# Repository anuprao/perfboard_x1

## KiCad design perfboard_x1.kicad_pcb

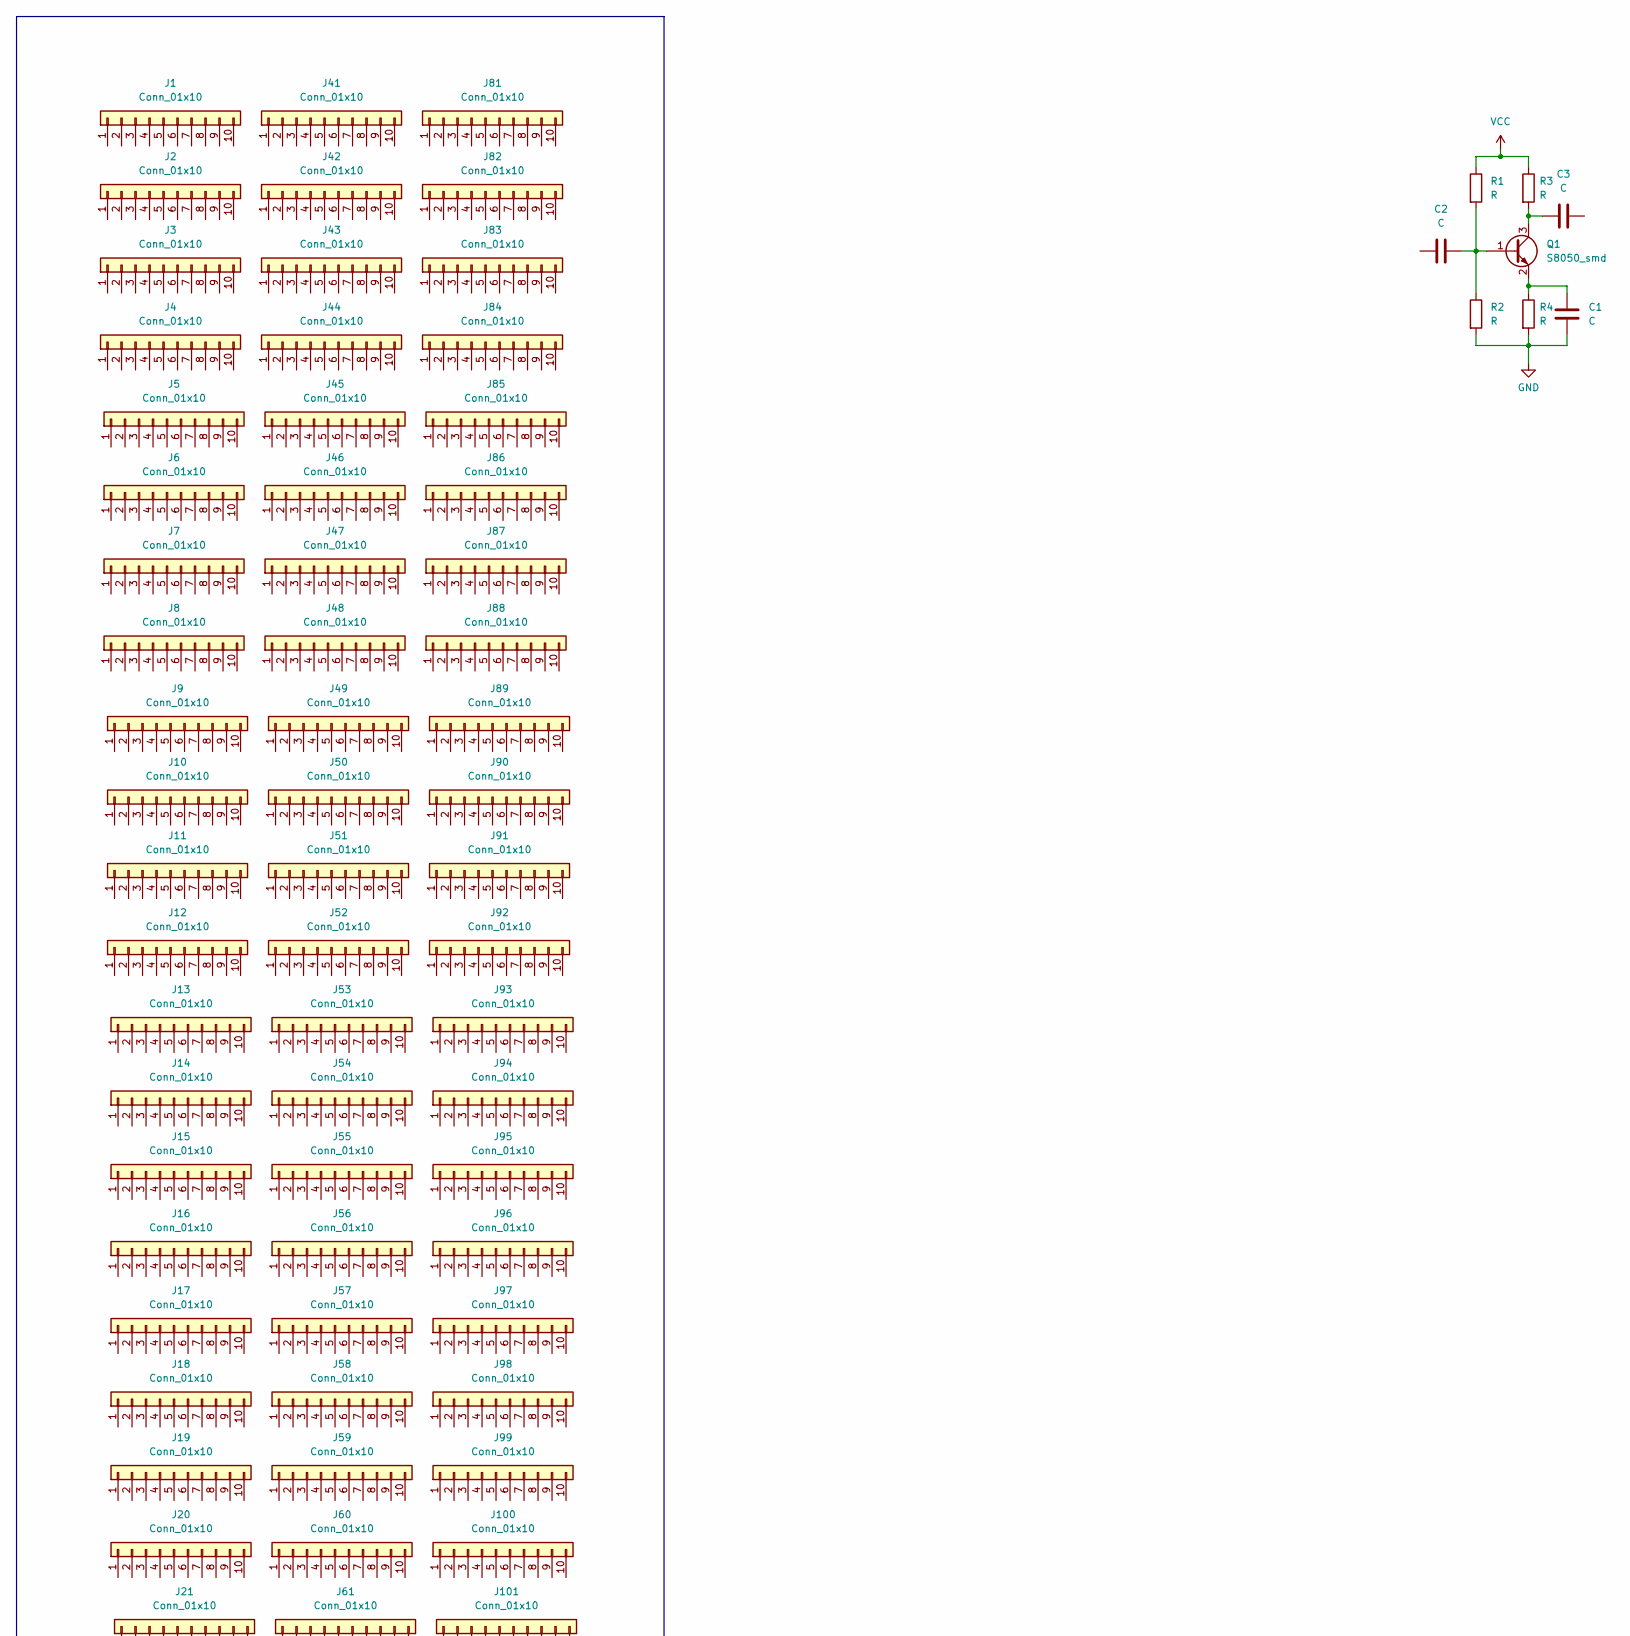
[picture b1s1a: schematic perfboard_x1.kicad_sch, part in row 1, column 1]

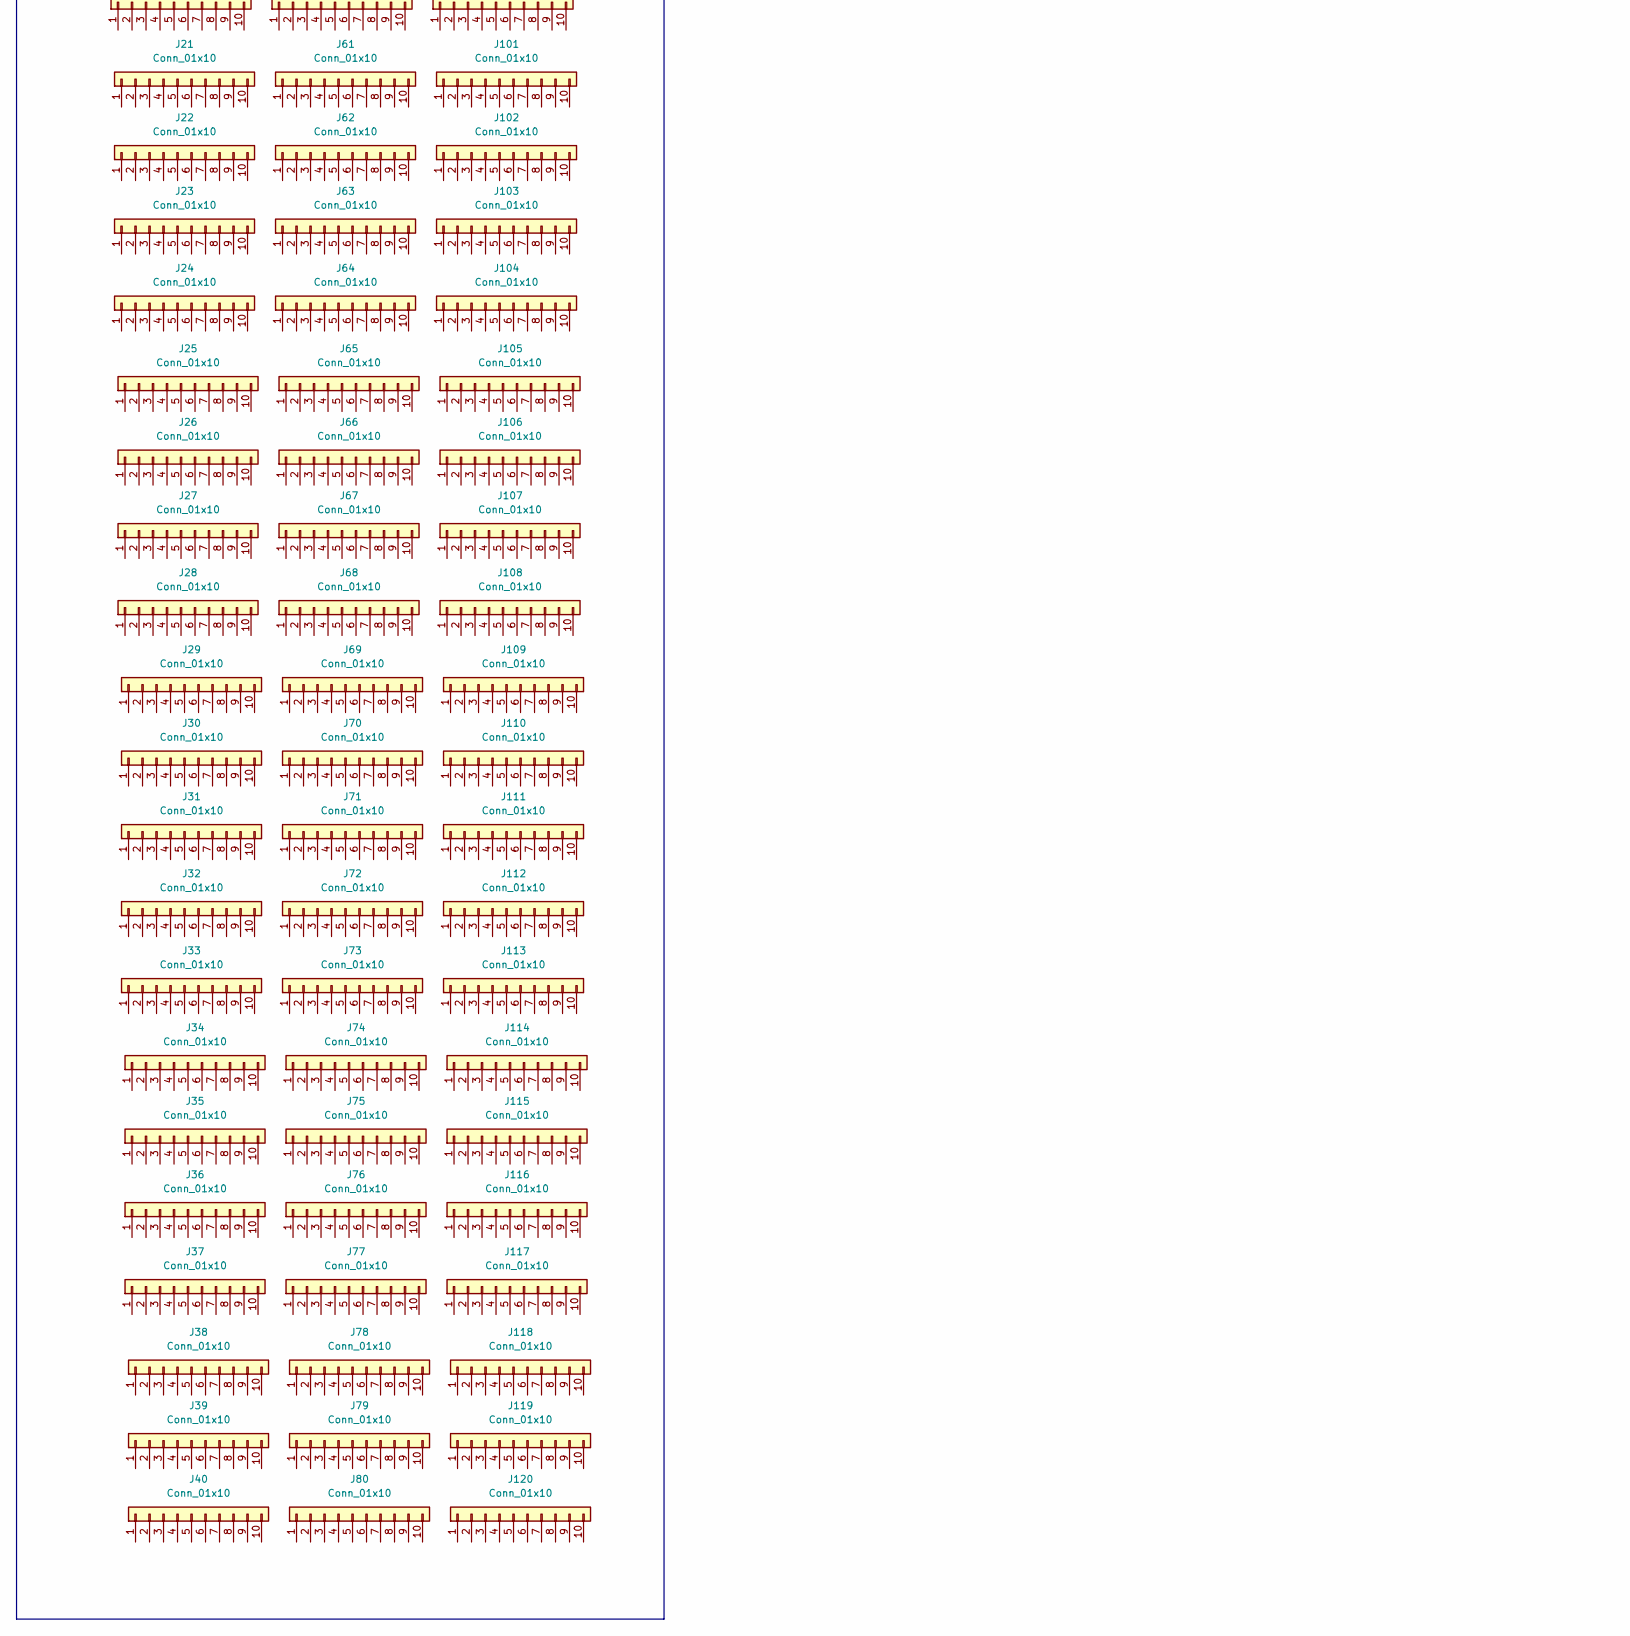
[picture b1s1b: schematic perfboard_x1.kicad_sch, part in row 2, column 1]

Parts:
C1, C2, C3: C; C_1206_3216Metric
J1, J2, J3, J4, J5, J6, J7, J8, J9, J10, J11, J12, J13, J14, J15, J16, J17, J18, J19, J20, J21, J22, J23, J24, J25, J26, J27, J28, J29, J30, J31, J32, J33, J34, J35, J36, J37, J38, J39, J40, J41, J42, J43, J44, J45, J46, J47, J48, J49, J50, J51, J52, J53, J54, J55, J56, J57, J58, J59, J60, J61, J62, J63, J64, J65, J66, J67, J68, J69, J70, J71, J72, J73, J74, J75, J76, J77, J78, J79, J80, J81, J82, J83, J84, J85, J86, J87, J88, J89, J90, J91, J92, J93, J94, J95, J96, J97, J98, J99, J100, J101, J102, J103, J104, J105, J106, J107, J108, J109, J110, J111, J112, J113, J114, J115, J116, J117, J118, J119, J120: Conn_01x10; mypad_100_plain
Q1: S8050_smd; SOT-23_alternate_handsoldering
R1, R2, R3, R4: R; R_1206_3216Metric

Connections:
GND: C1.2, R2.2, R4.2
unnamed: C2.2, Q1.1 (B), R1.2, R2.1
unnamed: C3.1, Q1.3 (C), R3.2
unnamed: C1.1, Q1.2 (E), R4.1
VCC: R1.1, R3.1

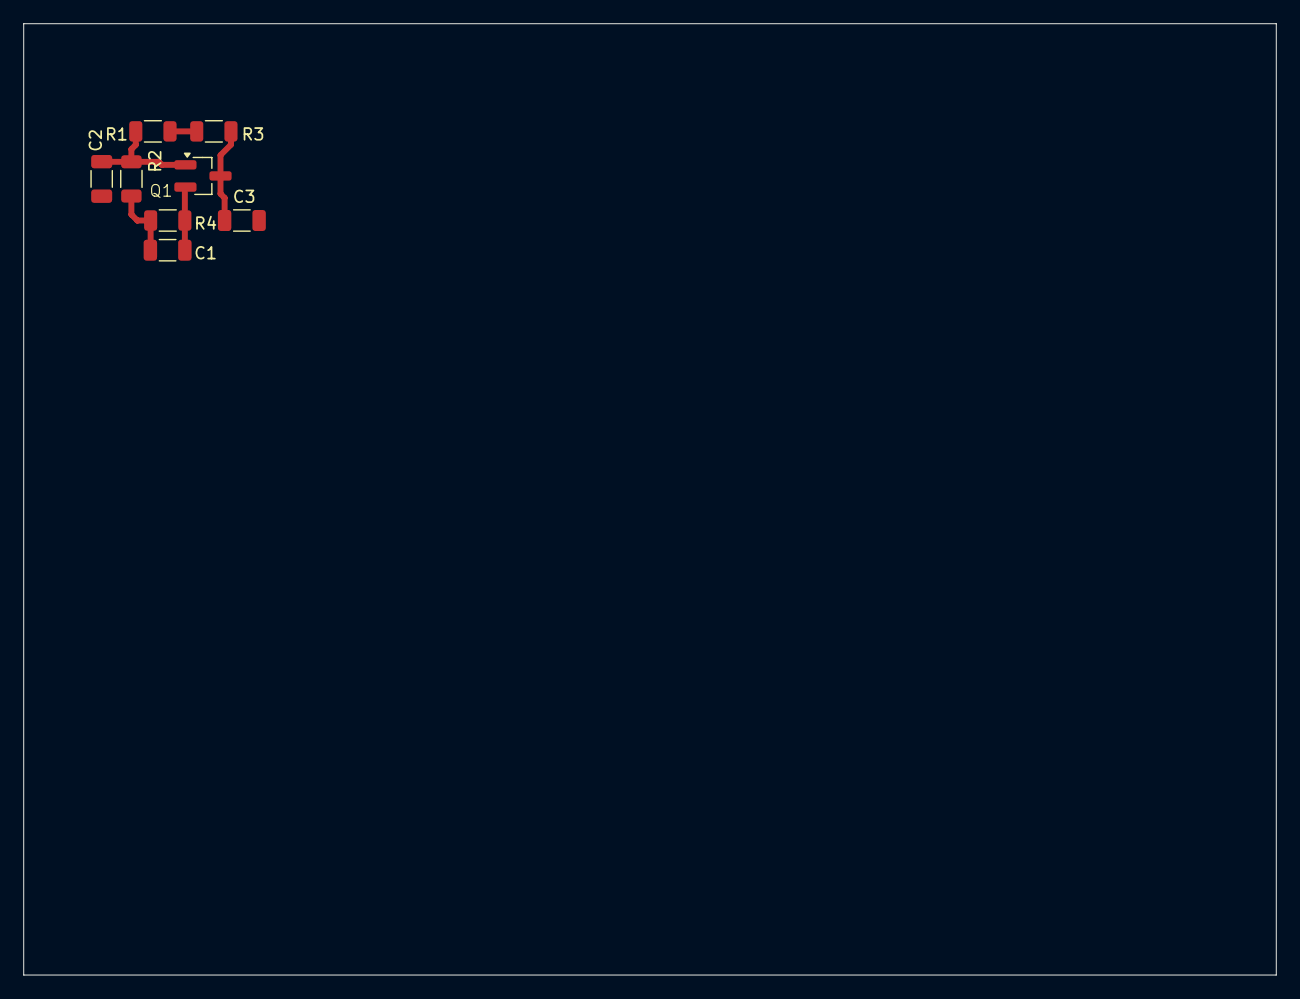
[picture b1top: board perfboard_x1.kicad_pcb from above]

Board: 2 copper layers, 107.1 x 81.3 mm, 128 parts (0 on the bottom side), 5 nets.

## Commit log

2025-02-27 Added initial files
2025-02-27 Added a sample circuit
